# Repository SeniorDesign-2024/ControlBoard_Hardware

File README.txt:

Senior Design Control Board

The purpose of this board is to interface with all the different subsystems and manage inputs and outputs to and from the user.

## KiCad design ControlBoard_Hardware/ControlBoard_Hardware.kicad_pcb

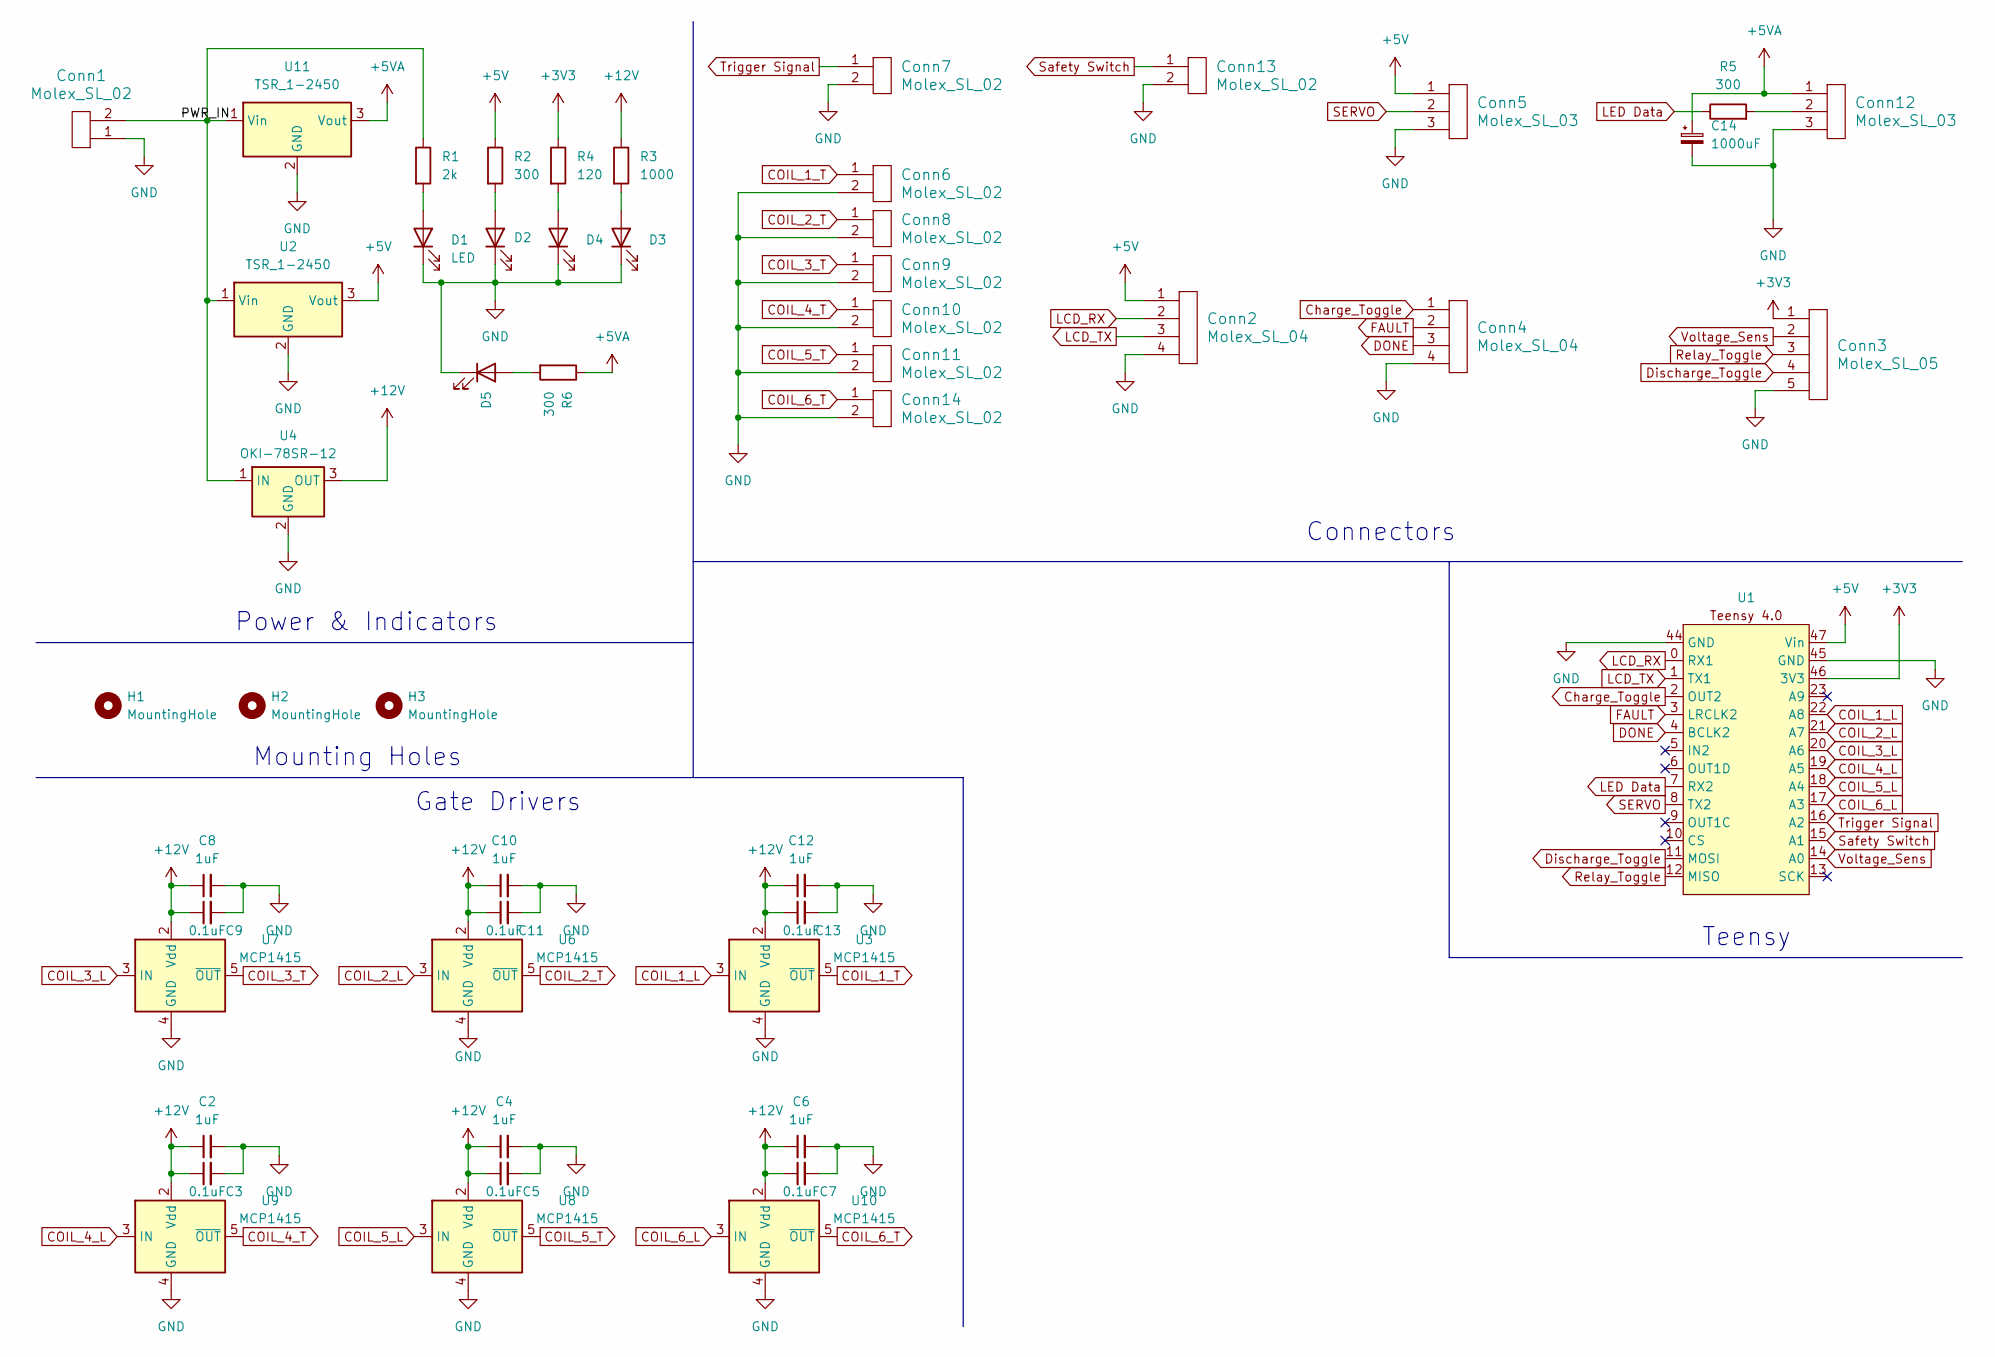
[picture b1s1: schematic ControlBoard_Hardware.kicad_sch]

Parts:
C2, C4, C6, C8, C10, C12: 1uF; C_0603_1608Metric_Pad1.08x0.95mm_HandSolder
C3, C5, C7, C9, C11, C13: 0.1uF; C_0603_1608Metric_Pad1.08x0.95mm_HandSolder
C14: 1000uF; CP_Radial_D8.0mm_P3.50mm
Conn1, Conn6, Conn7, Conn8, Conn9, Conn10, Conn11, Conn13, Conn14: Molex_SL_02; MOLEX_SL_02_Horizontal
Conn2, Conn4: Molex_SL_04; MOLEX_SL_04_Horizontal
Conn3: Molex_SL_05; MOLEX_SL_05_Horizontal
Conn5, Conn12: Molex_SL_03; MOLEX_SL_03_Horizontal
D1, D2, D3, D4, D5: LED; LED_0603_1608Metric_Pad1.05x0.95mm_HandSolder
H1, H2, H3: MountingHole; MountingHole_3.2mm_M3
R1: 2k; R_0603_1608Metric_Pad0.98x0.95mm_HandSolder
R2, R5, R6: 300; R_0603_1608Metric_Pad0.98x0.95mm_HandSolder
R3: 1000; R_0603_1608Metric_Pad0.98x0.95mm_HandSolder
R4: 120; R_0603_1608Metric_Pad0.98x0.95mm_HandSolder
U1: Teensy_4_0
U2, U11: TSR_1-2450; Converter_DCDC_TRACO_TSR-1_THT
U3, U6, U7, U8, U9, U10: MCP1415; SOT-23-5
U4: OKI-78SR-12; Converter_DCDC_Murata_OKI-78SR_Horizontal

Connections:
+3V3: Conn3.1, R4.1, U1.46 (3V3)
+5V: Conn2.1, Conn5.1, R2.1, U1.47 (Vin), U2.3 (Vout)
+5VA: C14.1, Conn12.1, R6.1, U11.3 (Vout)
+12V: C2.1, C3.1, C4.1, C5.1, C6.1, C7.1, C8.1, C9.1, C10.1, C11.1, C12.1, C13.1, R3.1, U3.2 (Vdd), U4.3 (OUT), U6.2 (Vdd), U7.2 (Vdd), U8.2 (Vdd), U9.2 (Vdd), U10.2 (Vdd)
/PWR_IN: Conn1.2, R1.1, U2.1 (Vin), U4.1 (IN), U11.1 (Vin)
COIL_1_L: U1.22 (A8), U3.3 (IN)
COIL_1_T: Conn6.1, U3.5 (~OUT)
COIL_2_L: U1.21 (A7), U6.3 (IN)
COIL_2_T: Conn8.1, U6.5 (~OUT)
COIL_3_L: U1.20 (A6), U7.3 (IN)
COIL_3_T: Conn9.1, U7.5 (~OUT)
COIL_4_L: U1.19 (A5), U9.3 (IN)
COIL_4_T: Conn10.1, U9.5 (~OUT)
COIL_5_L: U1.18 (A4), U8.3 (IN)
COIL_5_T: Conn11.1, U8.5 (~OUT)
COIL_6_L: U1.17 (A3), U10.3 (IN)
COIL_6_T: Conn14.1, U10.5 (~OUT)
Charge_Toggle: Conn4.1, U1.2 (OUT2)
DONE: Conn4.3, U1.4 (BCLK2)
Discharge_Toggle: Conn3.4, U1.11 (MOSI)
FAULT: Conn4.2, U1.3 (LRCLK2)
GND: C2.2, C3.2, C4.2, C5.2, C6.2, C7.2, C8.2, C9.2, C10.2, C11.2, C12.2, C13.2, C14.2, Conn1.1, Conn2.4, Conn3.5, Conn4.4, Conn5.3, Conn6.2, Conn7.2, Conn8.2, Conn9.2, Conn10.2, Conn11.2, Conn12.3, Conn13.2, Conn14.2, D1.1 (K), D2.1 (K), D3.1 (K), D4.1 (K), D5.1 (K), U1.44 (GND), U1.45 (GND), U2.2 (GND), U3.4 (GND), U4.2 (GND), U6.4 (GND), U7.4 (GND), U8.4 (GND), U9.4 (GND), U10.4 (GND), U11.2 (GND)
LCD_RX: Conn2.2, U1.0 (RX1)
LCD_TX: Conn2.3, U1.1 (TX1)
LED Data: R5.1, U1.7 (RX2)
unnamed: Conn12.2, R5.2
unnamed: D1.2 (A), R1.2
unnamed: D2.2 (A), R2.2
unnamed: D3.2 (A), R3.2
unnamed: D4.2 (A), R4.2
unnamed: D5.2 (A), R6.2
Relay_Toggle: Conn3.3, U1.12 (MISO)
SERVO: Conn5.2, U1.8 (TX2)
Safety Switch: Conn13.1, U1.15 (A1)
Trigger Signal: Conn7.1, U1.16 (A2)
Voltage_Sens: Conn3.2, U1.14 (A0)

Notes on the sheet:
Teensy
Power & Indicators
Connectors
Gate Drivers
Mounting Holes

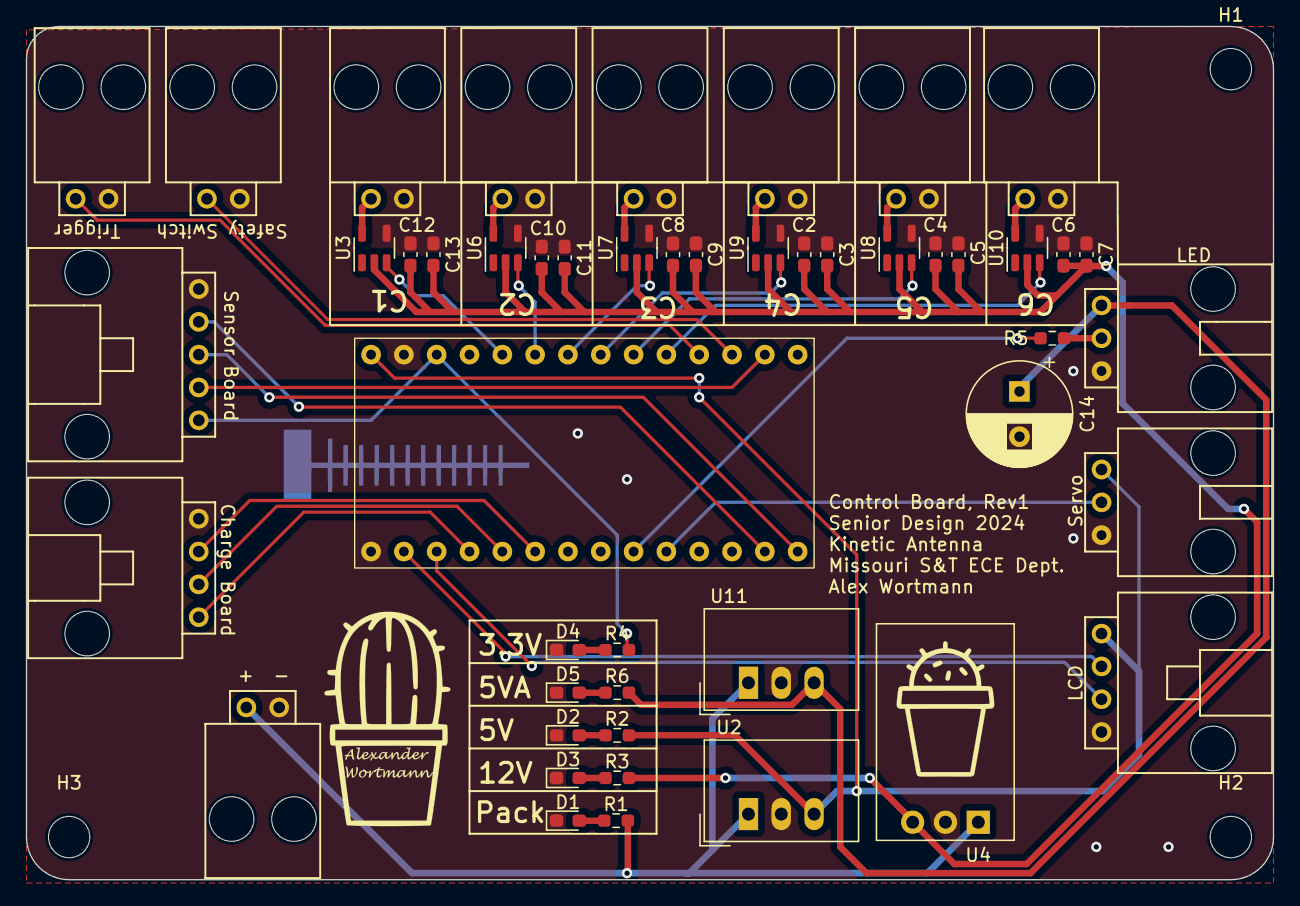
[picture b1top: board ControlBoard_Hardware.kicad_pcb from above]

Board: 2 copper layers, 96.5 x 66.0 mm, 51 parts (0 on the bottom side), 36 nets.

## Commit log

2023-11-17 Made schematic
2023-11-17 Assigned footprints
2023-11-17 Revert "Assigned footprints"
    This reverts commit 6f2e1c40c0d01355b4ad57b50ebbed6eef59f7aa.
2023-12-01 Made layout
2023-12-08 updatedfor final report
2024-01-23 Updated Schematic
2024-01-23 fixed voltage level on coil sensors
2024-02-11 started layout
2024-02-17 sus gate driver
2024-02-20 finished board layour
2024-02-20 added dimension marks
2024-02-20 Added silk screens
2024-02-20 something
2024-02-20 ahhhhhhhh
2024-02-22 changed review critiques
2024-02-23 created bom
2024-02-27 generated gerbs
2024-02-27 zipped gerbs
